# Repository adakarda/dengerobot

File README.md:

# ÇDTP iki tekerlekli hasta destek robotu — denge, hareket ve yanaşma

YTÜ EEF ÇDTP 2026-27 Güz. Kontrol bölümünün işi (denge, hareket, istasyona yaklaşma) ve onun dokunduğu her şey:
robot firmware'i, eldiven firmware'i, LQR tasarımı, fizik simülasyonu ve kabul testleri.

Parça listesi ve takımın ortak şeması: <https://cdtp-robot.netlify.app>. Buradaki pinler o şemayla aynıdır;
farklar `docs/` altındaki plan sayfasında "değişiklik önerisi" olarak işaretli.

## Klasörler

| Klasör | İçerik |
|---|---|
| `common/cdtp_core/` | Donanımdan bağımsız çekirdek: mod makinesi, LQR denge, hareket adımları, IR yanaşma, eldiven jesti, paket. **Robot, eldiven ve simülasyon aynı kodu kullanır.** |
| `firmware/robot/` | Robot ESP32 (WROOM-32D): MPU6050, PCNT enkoder/IR, BTS7960, ESP-NOW, Wi-Fi WebSocket |
| `firmware/glove/` | Eldiven ESP32-C3 Super Mini: MPU6050 → 5 komut → ESP-NOW 20 Hz |
| `tools/lqr_design.py` | Fiziksel model + LQR. `gains.h` ve simülasyon modelini üretir |
| `sim/` | Ters sarkaç + motor + sensör gürültüsü + IR istasyon simülasyonu, kabul testleri |
| `twin/` | MuJoCo dijital ikizi: robot firmware mantığı + 3B gövde, V-yuva, direk |
| `cad/` | 3B baskı: `olcu.py` (bütün ölçüler), `robot_cad.py` (STL + montaj denetimi), `stl/` (6 parça), `montaj.glb` |
| `elektronik/` | KiCad 10 projesi: `cdtp_robot.kicad_pro`, şema PDF/SVG, ERC ve netlist; `tools/kicad_sema.py` üretir |
| `docs/` | Robot yapım dosyası, PDF kitap, eski BLE protokolü (yerine WebSocket), grafikler |

## Hızlı başlangıç

```bash
python tools/lqr_design.py        # model değişince kazançları yeniden üret
bash tools/run_sim.sh             # 20 kabul testi + birim testleri (Git Bash / Linux)
python tools/plot_sim.py          # docs/img/*.png
python cad/robot_cad.py           # 3B parçalar + montaj denetimi (pip install manifold3d trimesh)
python tools/kicad_sema.py        # KiCad şeması + ERC + pins.h karşılaştırması (KiCad 10 gerekir)
python tools/check_consistency.py # belge, kod, 3B model ve şema tutarlılığı
```

Firmware: VS Code + PlatformIO eklentisi → `firmware/robot` (ya da `firmware/glove`) klasörünü açın → Upload.
Kod yüklerken robotta **JP1 köprüsünü çıkarın**, eldivende **SW1'i kapatın**.

## İlk çalıştırma sırası (robot)

1. **Motorsuz:** EN kablosu takılı değilken yükleyin. Seri monitörde (115200) jiroskop kalibrasyonu ve
   `Robot MAC` satırını görün. MAC'i `firmware/glove/src/main.cpp` içindeki `ROBOT_MAC`'e yazın.
2. **IMU yönü:** robotu elle öne eğin → telemetride `tilt` artmalı. Azalıyorsa `imu_filter.h > AxisMap`
   işaretlerini çevirin. Sola döndürün → `yaw` artmalı.
3. **Enkoder:** tekeri elle 10 tur ileri çevirin → `x` ≈ 2,04 m. Değilse `ENC_COUNTS_PER_REV`; yön tersse
   `ENC_*_INVERT`.
4. **Motor yönü:** robotu tekerler havada kalacak şekilde destekleyin, seri porta `mtest` yazın: önce sol, sonra
   sağ teker 1'er saniye yavaşça **ileri** dönmeli. Ters dönen için `MOTOR_*_INVERT`.
5. **Model:** gövdeyi tartın, kütle merkezini (ip ile asarak) bulun → `tools/lqr_design.py` `P` sözlüğü →
   yeniden çalıştırın → simülasyon testlerinin hâlâ geçtiğini görün → yükleyin.
6. **Denge noktası:** robotu elle en rahat durduğu açıda tutun, seri porta `cal` yazın.
7. Tamamen bitince `main.cpp` içinde `FREEZE = true` (finalde parametre değiştirilemez).

## Seri komutlar

`stat` · `mtest` · `task=0..3` · `glove=step|cont` · `cal` · `vscale=1.000`

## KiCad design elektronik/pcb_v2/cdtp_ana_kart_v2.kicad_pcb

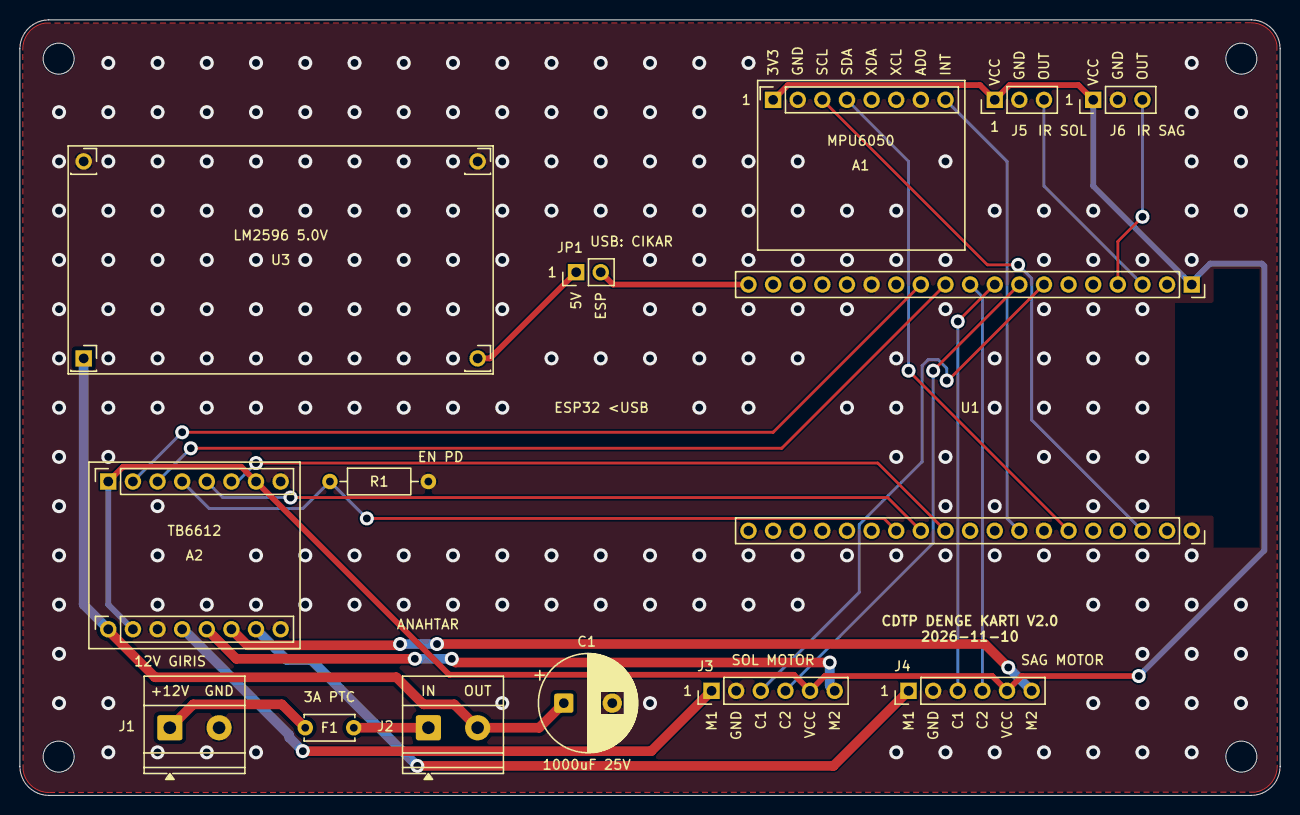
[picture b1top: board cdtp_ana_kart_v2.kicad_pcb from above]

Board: 2 copper layers, 130.0 x 80.0 mm, 18 parts (0 on the bottom side), 25 nets.

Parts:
A1: GY-521 MPU6050 (1x8 soket); PinSocket_1x08_P2.54mm_Vertical
A2: TB6612FNG modul (2x8 soket); TB6612_2x8_PinSocket_P2.54mm
C1: 1000uF 25V; CP_Radial_D10.0mm_P5.00mm
F1: PTC sigorta 3 A; C_Disc_D5.0mm_W2.5mm_P5.00mm
H1, H2, H3, H4: M3; MountingHole_3.2mm_M3
J1: 12V ADAPTOR GIRIS klemens; TerminalBlock_Phoenix_MKDS-1,5-2-5.08_1x02_P5.08mm_Horizont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
J2: ANAHTAR klemens; TerminalBlock_Phoenix_MKDS-1,5-2-5.08_1x02_P5.08mm_Horizont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
J3: SOL MOTOR 6 pin; PinHeader_1x06_P2.54mm_Vertical
J4: SAG MOTOR 6 pin; PinHeader_1x06_P2.54mm_Vertical
J5: IR SOL; PinHeader_1x03_P2.54mm_Vertical
J6: IR SAG; PinHeader_1x03_P2.54mm_Vertical
JP1: USB'de cikar; PinHeader_1x02_P2.54mm_Vertical
R1: 10k; R_Axial_DIN0207_L6.3mm_D2.5mm_P10.16mm_Horizontal
U1: ESP32-WROOM-32D DevKitC 38 pin; ESP32_DevKitC_2x19_PinSocket_P2.54mm
U3: LM2596 mini 5,0 V (4 ped); LM2596_mini_4pad

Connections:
/+3V3: A1.1, A2.1, A2.7, A2.10, J3.5, J4.5, J5.1, J6.1, U1.1
/+5V: JP1.1, U3.3
/+5V_ESP: JP1.2, U1.19
/+12V: A2.9, C1.1, J2.2, U3.1
/ADP+: F1.1, J1.1
/ENC_L_A: J3.3, U1.7
/ENC_L_B: J3.4, U1.8
/ENC_R_A: J4.3, U1.9
/ENC_R_B: J4.4, U1.10
/FUSED: F1.2, J2.1
/GND: A1.2, A1.7, A2.8, A2.11, A2.16, C1.2, J1.2, J3.2, J4.2, J5.2, J6.2, R1.2, U1.14, U1.20, U1.26, U3.2, U3.4
/I2C_SCL: A1.3, U1.22
/I2C_SDA: A1.4, U1.25
/IMU_INT: A1.8, U1.27
/IR_L: J5.3, U1.3
/IR_R: J6.3, U1.4
/L_LPWM: A2.2, U1.12
/L_RPWM: A2.3, U1.11
/MOTOR_EN: A2.4, R1.1, U1.32
/MOT_L+: A2.12, J3.1
/MOT_L-: A2.13, J3.6
/MOT_R+: A2.15, J4.1
/MOT_R-: A2.14, J4.6
/R_LPWM: A2.6, U1.30
/R_RPWM: A2.5, U1.31

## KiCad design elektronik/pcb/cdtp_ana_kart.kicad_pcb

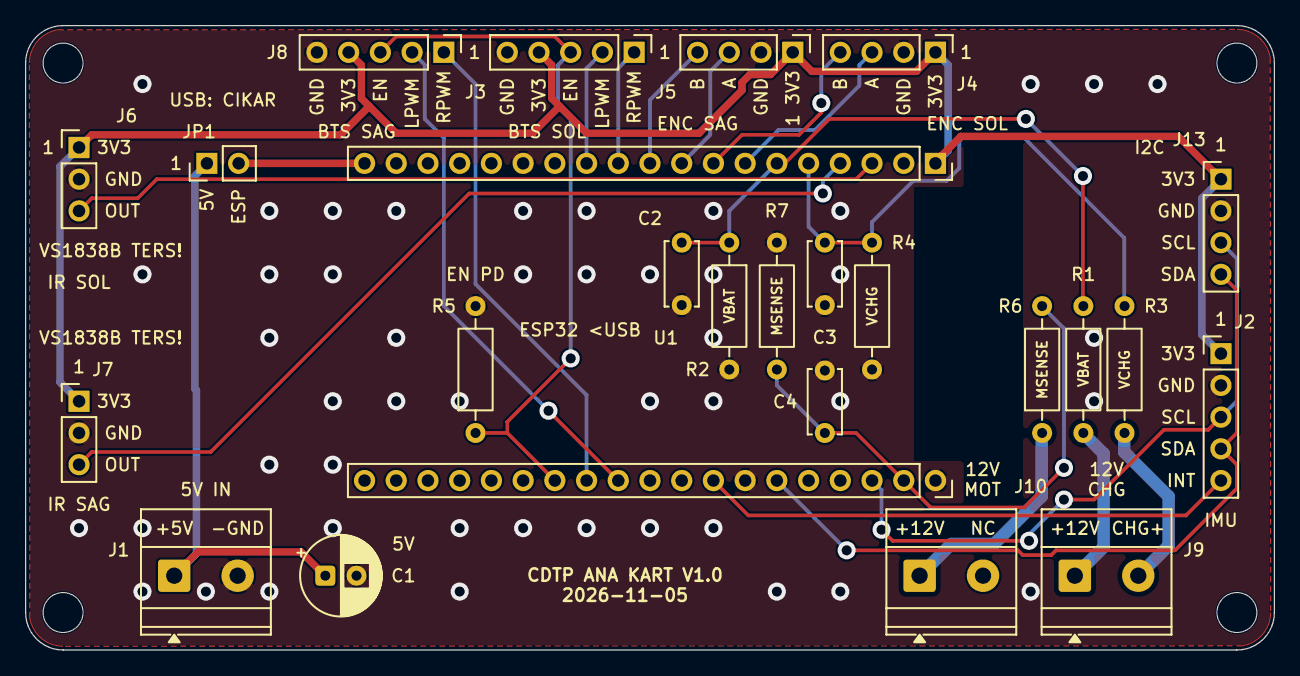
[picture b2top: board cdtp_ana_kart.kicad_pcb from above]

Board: 2 copper layers, 100.0 x 50.0 mm, 28 parts (0 on the bottom side), 24 nets.

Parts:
C1: 100uF 16V; CP_Radial_D6.3mm_P2.50mm
C2, C3, C4: 100nF; C_Disc_D5.0mm_W2.5mm_P5.00mm
H1, H2, H3, H4: M3; MountingHole_3.2mm_M3
J1: 5 V klemens; TerminalBlock_Phoenix_MKDS-1,5-2-5.08_1x02_P5.08mm_Horizont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
J2: IMU; PinHeader_1x05_P2.54mm_Vertical
J3: BTS sol; PinHeader_1x05_P2.54mm_Vertical
J4: Enkoder sol; PinHeader_1x04_P2.54mm_Vertical
J5: Enkoder sag; PinHeader_1x04_P2.54mm_Vertical
J6: GENISLEME: IR goz sol (bos); PinHeader_1x03_P2.54mm_Vertical
J7: GENISLEME: IR goz sag (bos); PinHeader_1x03_P2.54mm_Vertical
J8: BTS sag; PinHeader_1x05_P2.54mm_Vertical
J9: GENISLEME: sarj girisi (bos); TerminalBlock_Phoenix_MKDS-1,5-2-5.08_1x02_P5.08mm_Horizont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
J10: Motor hatti klemens; TerminalBlock_Phoenix_MKDS-1,5-2-5.08_1x02_P5.08mm_Horizont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
J13: GENISLEME: I2C (ekran, 2. sensor); PinHeader_1x04_P2.54mm_Vertical
JP1: USB'de cikar; PinHeader_1x02_P2.54mm_Vertical
R1, R3, R6: 100k; R_Axial_DIN0207_L6.3mm_D2.5mm_P10.16mm_Horizontal
R2, R4: 27k; R_Axial_DIN0207_L6.3mm_D2.5mm_P10.16mm_Horizontal
R5: 10k; R_Axial_DIN0207_L6.3mm_D2.5mm_P10.16mm_Horizontal
R7: 33k; R_Axial_DIN0207_L6.3mm_D2.5mm_P10.16mm_Horizontal
U1: ESP32-WROOM-32D DevKitC; ESP32_DevKitC_2x19_PinSocket_P2.54mm

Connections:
/+3V3: J2.1, J3.4, J4.1, J5.1, J6.1, J7.1, J8.4, J13.1, U1.1
/+5V: C1.1, J1.1, JP1.1
/+5V_ESP: JP1.2, U1.19
/+12V: J9.1, R1.1
/+12V_MOT: J10.1, R6.1
/CHG+: J9.2, R3.1
/ENC_L_A: J4.3, U1.7
/ENC_L_B: J4.4, U1.8
/ENC_R_A: J5.3, U1.9
/ENC_R_B: J5.4, U1.10
/GND: C1.2, C2.2, C3.2, C4.2, J1.2, J2.2, J3.5, J4.2, J5.2, J6.2, J7.2, J8.5, J13.2, R2.2, R4.2, R5.2, R7.2, U1.14, U1.20, U1.26
/I2C_SCL: J2.3, J13.3, U1.22
/I2C_SDA: J2.4, J13.4, U1.25
/IMU_INT: J2.5, U1.27
/IR_L: J6.3, U1.3
/IR_R: J7.3, U1.4
/L_LPWM: J3.2, U1.12
/L_RPWM: J3.1, U1.11
/MOTOR_EN: J3.3, J8.3, R5.1, U1.32
/MOTOR_SENSE: C4.1, R6.2, R7.1, U1.21
/R_LPWM: J8.2, U1.30
/R_RPWM: J8.1, U1.31
/VBAT_ADC: C2.1, R1.2, R2.1, U1.6
/VCHG_ADC: C3.1, R3.2, R4.1, U1.5

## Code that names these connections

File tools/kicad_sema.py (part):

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        if m:
            esp_pin[int(m.group(1))] = num
    beklenen = {  # pins.h sabiti -> (hat, ulasmasi gereken uclar)
        "PIN_SDA": ("I2C_SDA", [("A1", "4"), ("J2", "4")]), "PIN_SCL": ("I2C_SCL", [("A1", "3"), ("J2", "3")]),
        "PIN_IMU_INT": ("IMU_INT", [("A1", "8"), ("J2", "5")]),
        "PIN_L_RPWM": ("L_RPWM", [("A2", "1"), ("J3", "1")]), "PIN_L_LPWM": ("L_LPWM", [("A2", "2"), ("J3", "2")]),
        "PIN_R_RPWM": ("R_RPWM", [("A3", "1"), ("J8", "1")]), "PIN_R_LPWM": ("R_LPWM", [("A3", "2"), ("J8", "2")]),
        "PIN_MOTOR_EN": ("MOTOR_EN", [("A2", "3"), ("A2", "4"), ("A3", "3"), ("A3", "4"), ("J3", "3"), ("J8", "3"), ("R5", "1")]),
        "PIN_ENC_L_A": ("ENC_L_A", [("M1", "3"), ("J4", "3")]), "PIN_ENC_L_B": ("ENC_L_B", [("M1", "4"), ("J4", "4")]),
        "PIN_ENC_R_A": ("ENC_R_A", [("M2", "3"), ("J5", "3")]), "PIN_ENC_R_B": ("ENC_R_B", [("M2", "4"), ("J5", "4")]),
        "PIN_IR_L": ("IR_L", [("J6", "3")]), "PIN_IR_R": ("IR_R", [("J7", "3")]),
        "PIN_VBAT": ("VBAT_ADC", [("R1", "2"), ("R2", "1"), ("C2", "1")]),
        "PIN_VCHG": ("VCHG_ADC", [("R3", "2"), ("R4", "1"), ("C3", "1")]),
        "PIN_MOTOR_SENSE": ("MOTOR_SENSE", [("R6", "2"), ("R7", "1"), ("C4", "1")]),
    }
    eksik = []
    for k, gpio in sabit.items():
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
